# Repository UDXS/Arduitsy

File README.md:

# Arduitsy
## A Tiny Arduino Dev Board By David Markarian
---
### A tiny Arduino Development Board that can fit in every project and is meant to power your smaller projects (Can be programmed by Arduino)
---
#### Specs
* Reset Button
* Atmel ATtiny85 (It's Arduino Compatible!)
* 5 programmable pins
* 2 PWM pins
* 3 Analog Read pins
* All can be used as digital
* ICSP(In-Circuit Serial Programming) lets you program it with any ICSP programmer or even any Arduino using ArduinoISP (Requires jumper wires)! [Link](http://highlowtech.org/?p=1695)
* JST-PH connector which means you can connect any LiPo or Battery Pack to it

---
#### Ingredients Required
* 2x 10k ohm 0805 surface-mount resistors
* 1x .1uF 0805 surface-mount capacitor
* 1x ATtiny85 8-SOIC
* 1x 2x03 male header
* 1x Surface Mount Reset Button
* 1x 0805 LED (Orange recommended)
* 2x 1X04 stacking (male & female) headers (recommended)

OR (instead of stacking headers)
* 2x 1X04 male headers

OR
* 2x 1X04 female headers

Note: You may have to purchase larger headers then break them up

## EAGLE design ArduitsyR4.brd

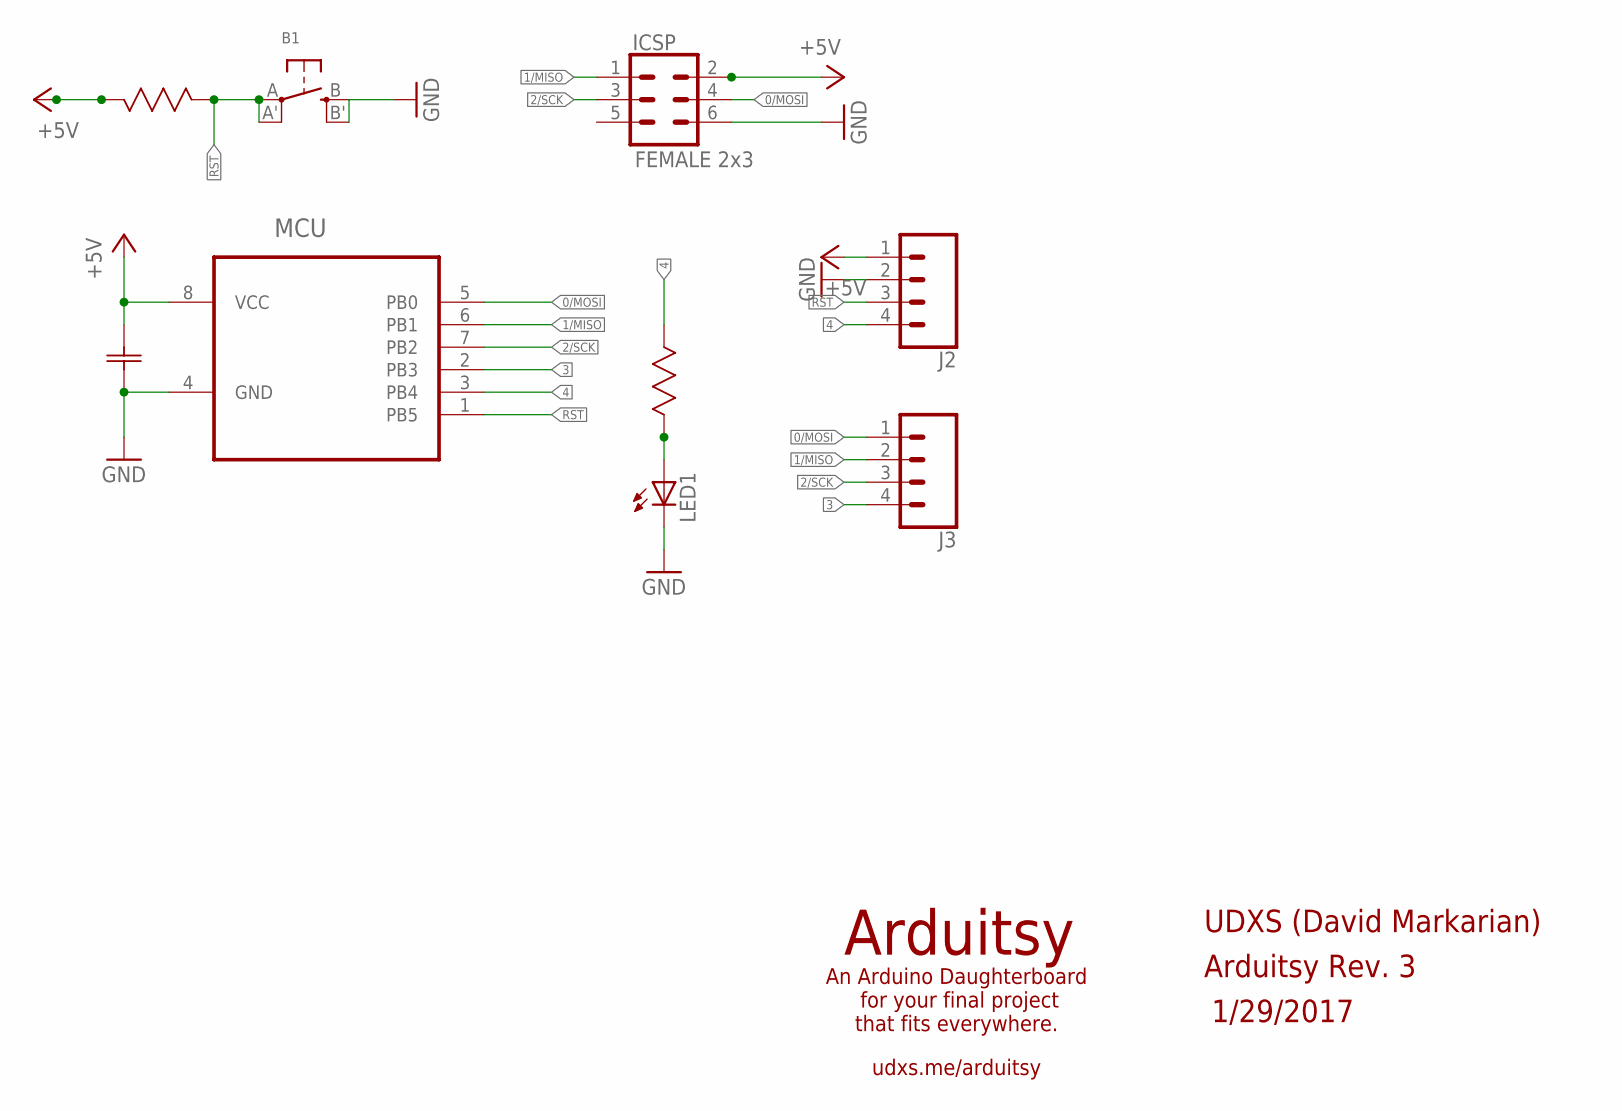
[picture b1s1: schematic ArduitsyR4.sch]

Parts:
B1: SWITCH_TACT_SMT; EVQ-Q2
C1: 0.1µF; CAPC2012X94N
ICSP: FEMALE 2x3; 2X3
J2, J3: CONN_04; 1X04
LED1: LEDCHIPLED_0805; CHIPLED_0805
MCU: ATTINY85-20SU; SOIC127P798X216-8N
R1, R2: 10K Ohms; RESC2013X65N

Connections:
0/MOSI: ICSP.4, J3.1, MCU.5 (PB0)
1/MISO: ICSP.1, J3.2, MCU.6 (PB1)
2/SCK: ICSP.3, J3.3, MCU.7 (PB2)
3: J3.4, MCU.2 (PB3)
4: J2.4, MCU.3 (PB4), R2.1 (R1)
+5V: C1.1 (C1), ICSP.2, J2.1, MCU.8 (VCC), R1.1 (R1)
GND: B1.B (S), B1.B' (S1), C1.2 (C2), ICSP.6, J2.2, LED1.C, MCU.4 (GND)
unnamed: LED1.A, R2.2 (R2)
RST: B1.A, B1.A' (P1), J2.3, MCU.1 (PB5), R1.2 (R2)

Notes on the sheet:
Arduitsy
An Arduino Daughterboard for your final project that fits everywhere.
udxs.me/arduitsy
UDXS (David Markarian)
1/29/2017
Arduitsy Rev. 3

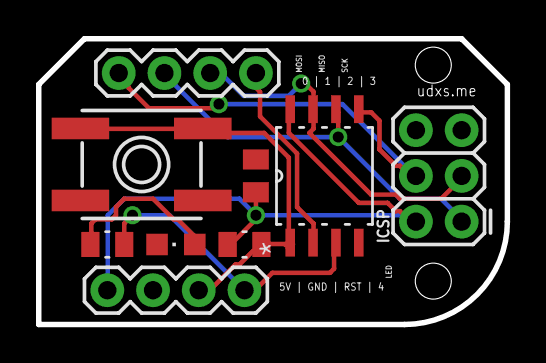
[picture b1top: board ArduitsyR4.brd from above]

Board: 2 copper layers, 26.0 x 15.9 mm, 9 parts (0 on the bottom side), 9 nets.

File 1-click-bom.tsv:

References	Qty	Description	Manufacturer	MPN	Manufacturer	MPN	Manufacturer	MPN	Manufacturer	MPN	Digikey	Mouser	RS	Newark	Farnell
B1	1	SMT Tact Switches	TE Connectivity / AMP	1571611-2							EG4374CT-ND	506FSM2JSMASTR	7561710	15N4498	1629606
C1	1	Capacitor 0805: .1uF		0805YC104KAT4A							478-7961-1-ND	5810805YC104K		94W2909	
ICSP	1	Male 2X03 Header (Female also works)		67996-406HLF							609-3218-ND	64967996406HLF		20M2191	1824424
J2, J3	2	Male/Female/Stacking 1X04 Header (stacking recommended)		SSQ-104-03-T-S							SAM1206-04-ND				
LED1	1	LED, Any Color (Orange recommended)		XZMOK54W-1							1497-1188-1-ND				
MCU	1	8-bit Microcontroller with In-System Programmable Flash		ATTINY85-20SU							ATTINY85-20SU-ND	5714551641		68T3810	1455164
R1, R2	2	RESISTOR 0805 10k ohms		MC0.1W08051%10K	Yageo	RC0805FR-0710KL	Panasonic	ERJ-6ENF1002V	Vishay	CRCW080510K0FKEA	P10.0KCCT-ND	667ERJ6ENF1002V	8123375	64R5370	1469856

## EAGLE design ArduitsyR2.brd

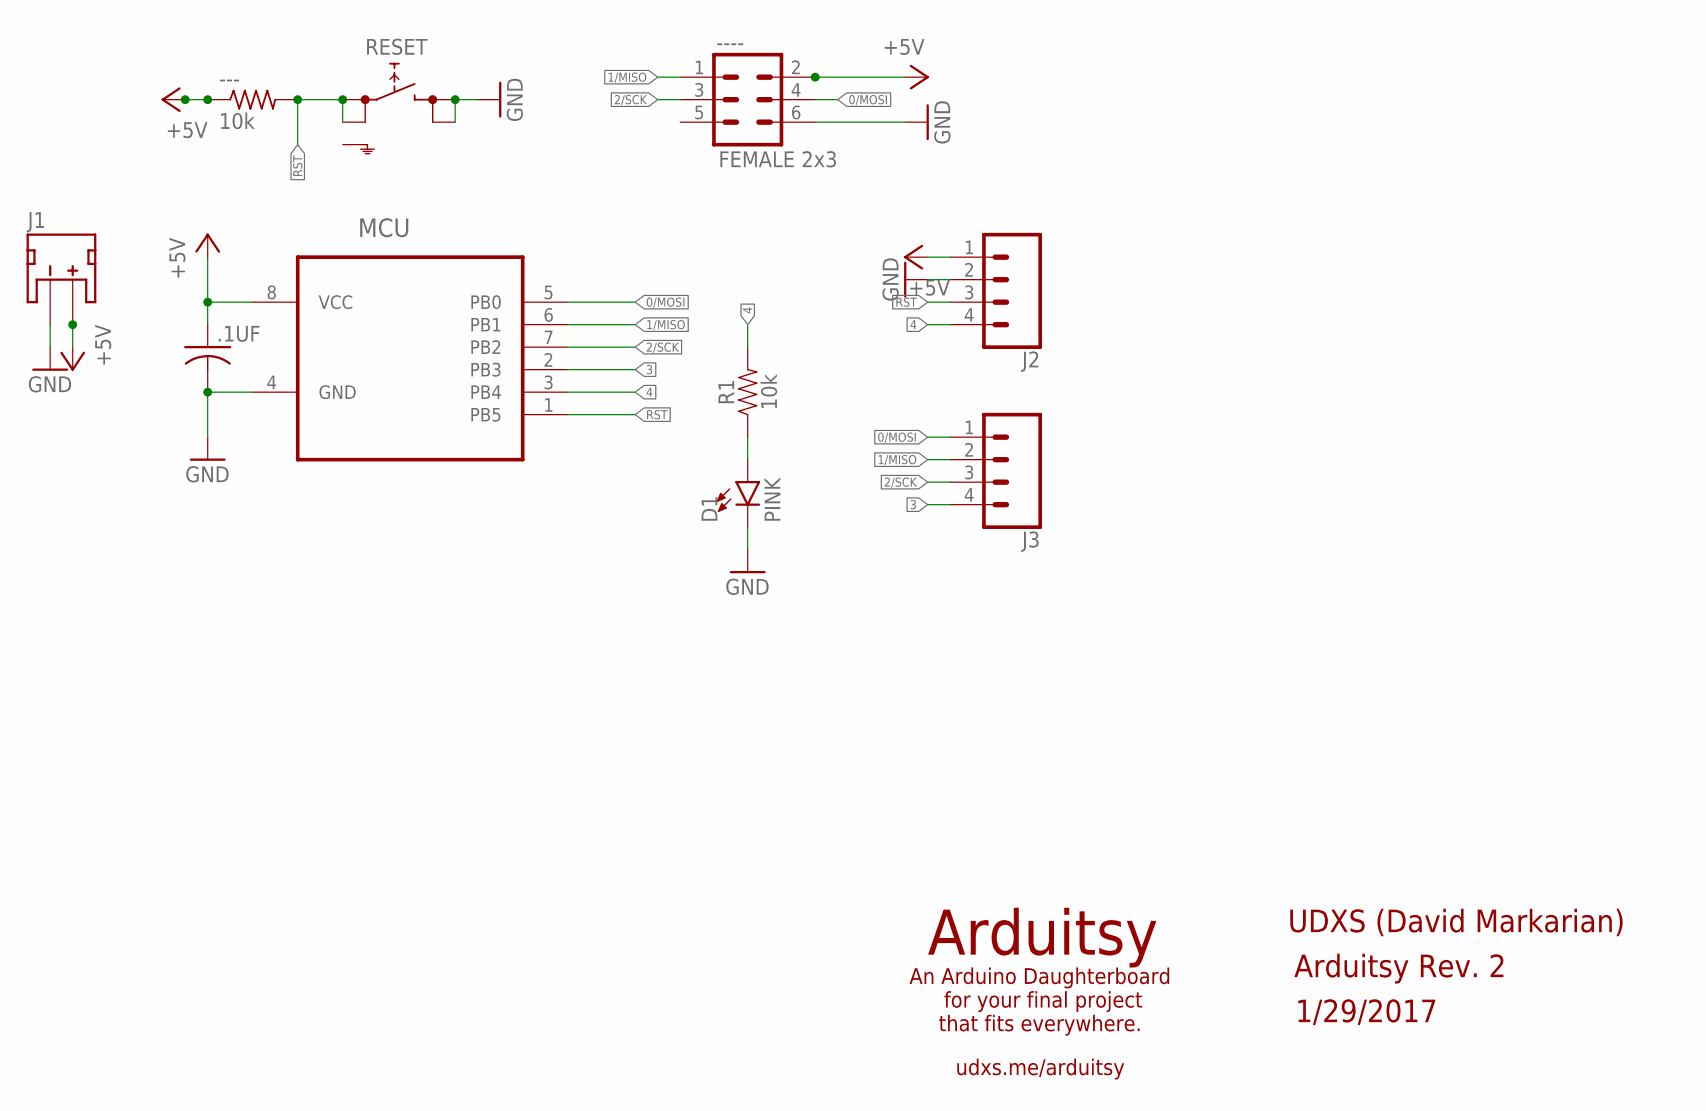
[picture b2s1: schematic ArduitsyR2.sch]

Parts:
---: 10k; M0805
----: FEMALE 2x3; 2X3
.1UF: C-USC0805; C0805
D1: PINK; LED-1206
J1: +5V; JST-2-SMD
J2, J3: CONN_04; 1X04
MCU: ATTINY85-20SU; SOIC127P798X216-8N
R1: 10k; 0603
RESET: SKHMPSE010; SKHMPXE010

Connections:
0/MOSI: ----.4, J3.1, MCU.5 (PB0)
1/MISO: ----.1, J3.2, MCU.6 (PB1)
2/SCK: ----.3, J3.3, MCU.7 (PB2)
3: J3.4, MCU.2 (PB3)
4: J2.4, MCU.3 (PB4), R1.2
+5V: ---.1, ----.2, .1UF.1, J1.2 (+), J2.1, MCU.8 (VCC)
GND: ----.6, .1UF.2, D1.C, J1.1 (-), J2.2, MCU.4 (GND), RESET.3 (2.1), RESET.4 (2.2)
unnamed: D1.A, R1.1
RST: ---.2, J2.3, MCU.1 (PB5), RESET.1 (1.1), RESET.2 (1.2)

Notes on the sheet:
Arduitsy
An Arduino Daughterboard for your final project that fits everywhere.
udxs.me/arduitsy
Arduitsy Rev. 2
UDXS (David Markarian)
1/29/2017

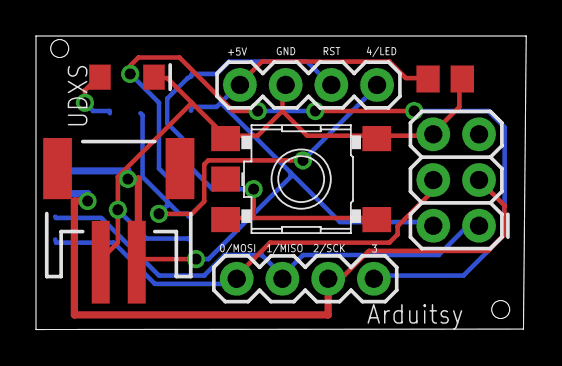
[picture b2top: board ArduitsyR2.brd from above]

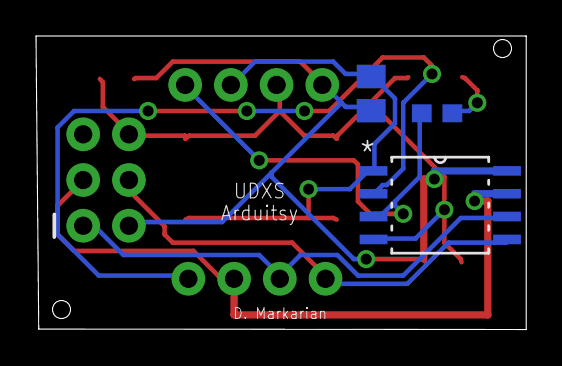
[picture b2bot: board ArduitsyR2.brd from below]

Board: 2 copper layers, 27.2 x 16.3 mm, 10 parts (3 on the bottom side), 9 nets.

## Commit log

2017-03-04 Set theme jekyll-theme-modernist

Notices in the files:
parts and their libraries:
SparkFun-Connectors: Licensing: Creative Commons ShareAlike 4.0 International - https://creativecommons.org/licenses/by-sa/4.0
microbuilder: This work is placed in the public domain, and may be freely used for commercial and non-commercial work with the following conditions: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
